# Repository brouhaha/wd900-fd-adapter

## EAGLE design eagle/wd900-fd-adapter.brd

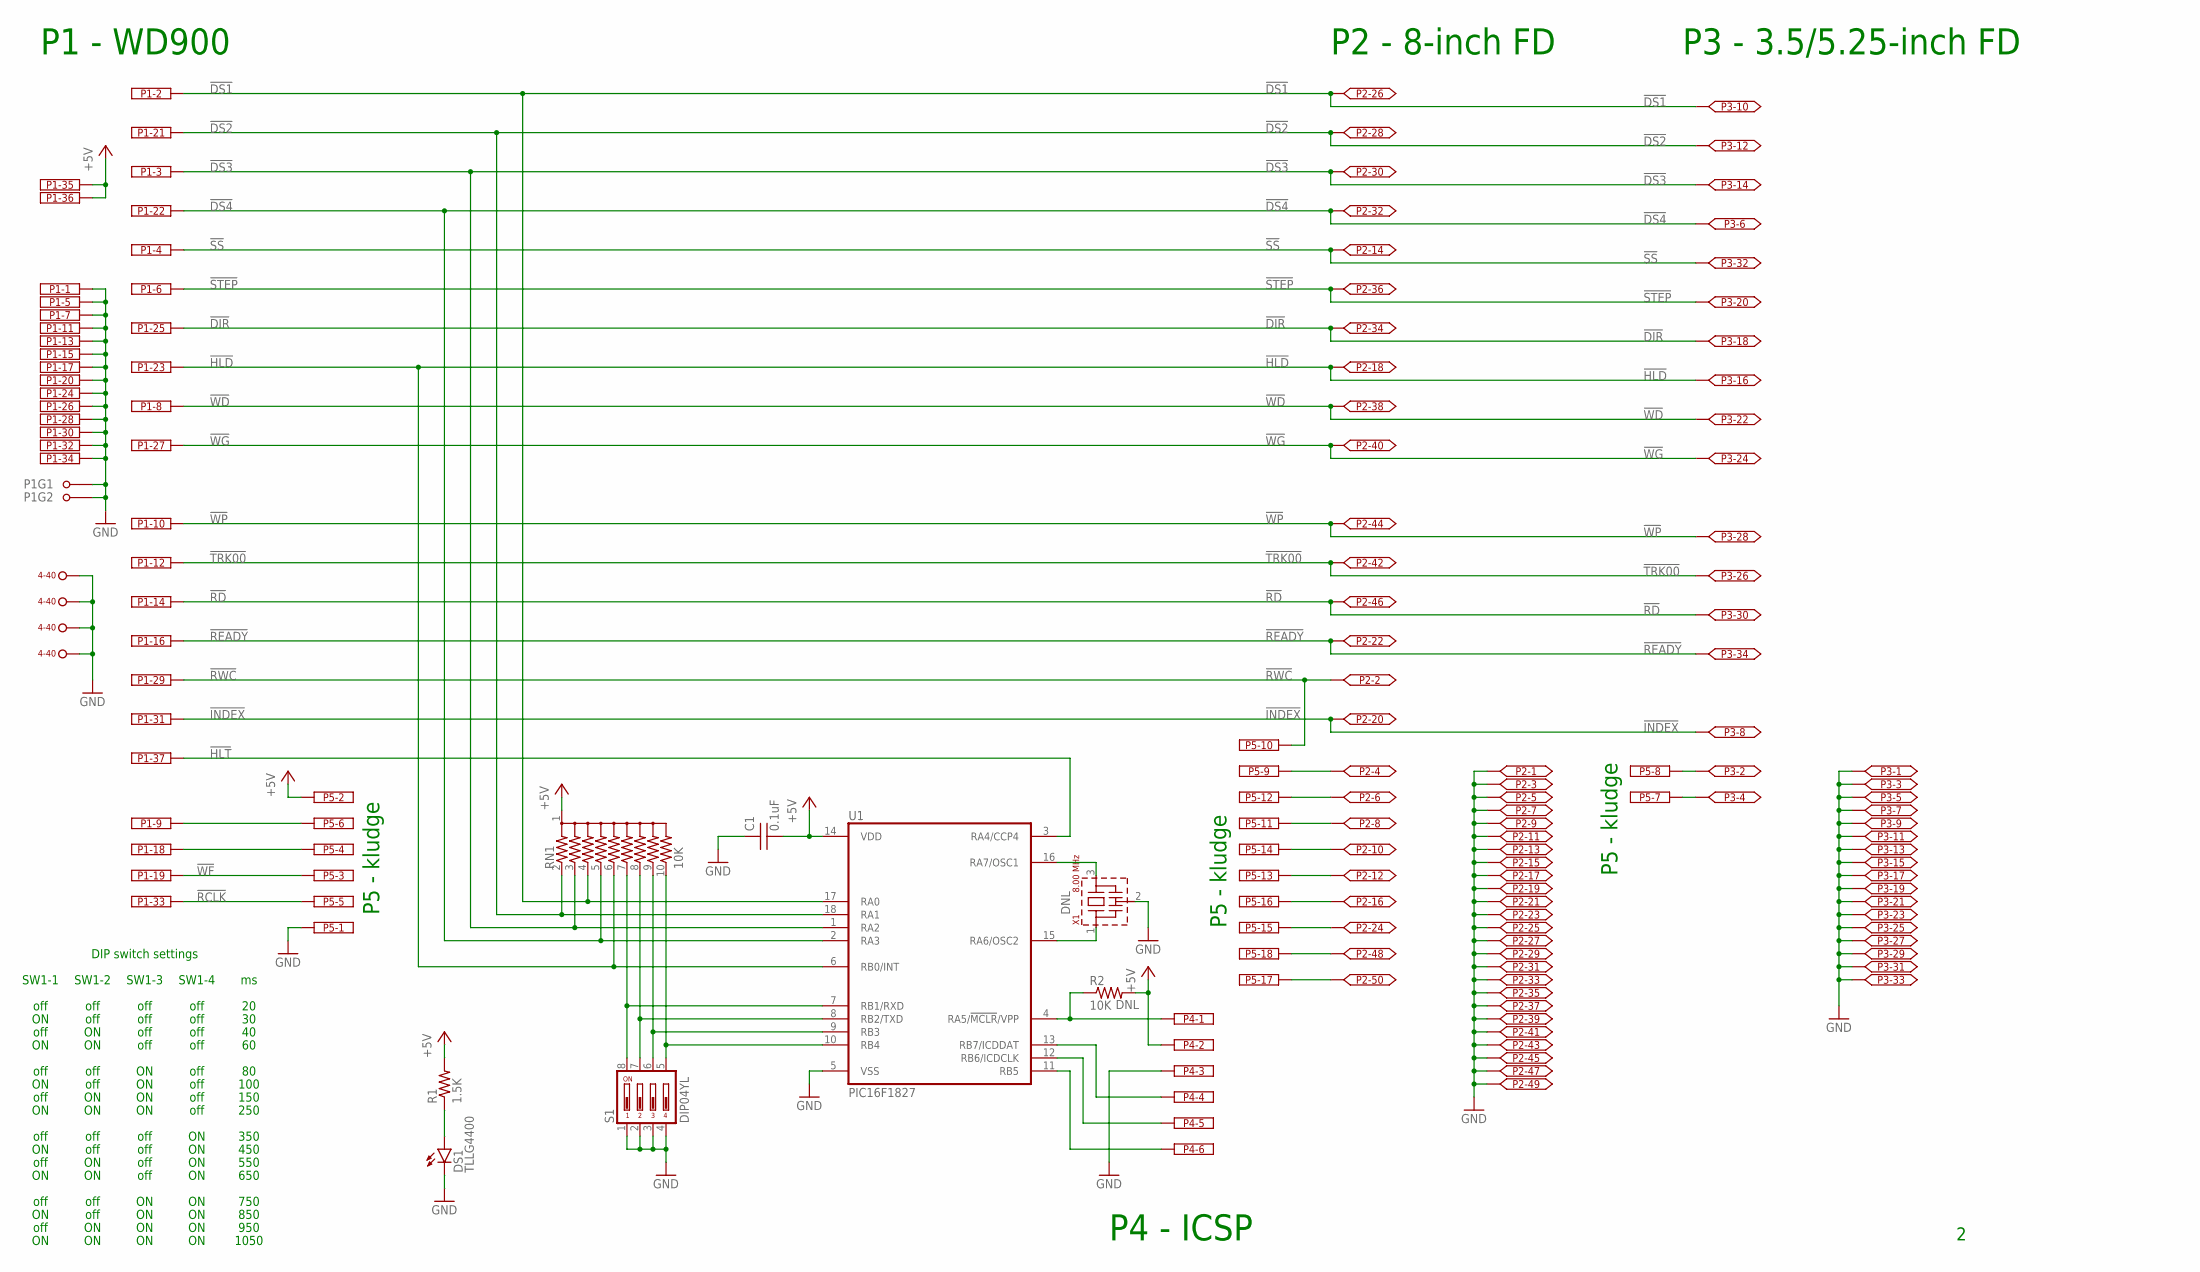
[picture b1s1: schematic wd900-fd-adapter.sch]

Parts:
C1: 0.1uF; C025-025X050
DS1: TLLG4400; LED3MM
H1, H2, H3, H4: HEX-4-40
P1: M37HPS; M37HP
P2: HDR-VS-2R-50
P3: HDR-VS-2R-34
P4: PIC ICSP; HDR-PIC-ICSP
P5: HDR-09-2
R1: 1.5K; 0207/10
R2: 10K; 0207/10
RN1: 10K; SIL10
S1: DIP04YL
U1: PIC16F1827; DIL18
X1: 8.00 MHz; CSTLS_G9

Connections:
!DIR: P1.25 (KL), P2.34, P3.18
!DS1: P1.2 (KL), P2.26, P3.10, RN1.4, U1.17 (RA0)
!DS2: P1.21 (KL), P2.28, P3.12, RN1.2, U1.18 (RA1)
!DS3: P1.3 (KL), P2.30, P3.14, RN1.3, U1.1 (RA2)
!DS4: P1.22 (KL), P2.32, P3.6, RN1.5, U1.2 (RA3)
!HLD: P1.23 (KL), P2.18, P3.16, RN1.6, U1.6 (RB0/INT)
!HLT: P1.37 (KL), U1.3 (RA4/CCP4)
!INDEX: P1.31 (KL), P2.20, P3.8
!RCLK: P1.33 (KL), P5.5
!RD: P1.14 (KL), P2.46, P3.30
!READY: P1.16 (KL), P2.22, P3.34
!RWC: P1.29 (KL), P2.2, P5.10
!SS: P1.4 (KL), P2.14, P3.32
!STEP: P1.6 (KL), P2.36, P3.20
!TRK00: P1.12 (KL), P2.42, P3.26
!WD: P1.8 (KL), P2.38, P3.22
!WF: P1.19 (KL), P5.3
!WG: P1.27 (KL), P2.40, P3.24
!WP: P1.10 (KL), P2.44, P3.28
+5V: C1.2, P1.35 (KL), P1.36 (KL), P4.2, P5.2, R1.2, R2.2, RN1.1, U1.14 (VDD)
GND: C1.1, DS1.K (C), H1.1, H2.1, H3.1, H4.1, P1.1 (KL), P1.5 (KL), P1.7 (KL), P1.11 (KL), P1.13 (KL), P1.15 (KL), P1.17 (KL), P1.20 (KL), P1.24 (KL), P1.26 (KL), P1.28 (KL), P1.30 (KL), P1.32 (KL), P1.34 (KL), P1.G1 (G2), P1.G2, P2.1, P2.3, P2.5, P2.7, P2.9, P2.11, P2.13, P2.15, P2.17, P2.19, P2.21, P2.23, P2.25, P2.27, P2.29, P2.31, P2.33, P2.35, P2.37, P2.39, P2.41, P2.43, P2.45, P2.47, P2.49, P3.1, P3.3, P3.5, P3.7, P3.9, P3.11, P3.13, P3.15, P3.17, P3.19, P3.21, P3.23, P3.25, P3.27, P3.29, P3.31, P3.33, P4.3, P5.1, S1.1, S1.2, S1.3, S1.4, U1.5 (VSS), X1.2 (VSS)
unnamed: P1.9 (KL), P5.6
unnamed: P1.18 (KL), P5.4
unnamed: RN1.7, S1.8, U1.7 (RB1/RXD)
unnamed: RN1.8, S1.7, U1.8 (RB2/TXD)
unnamed: RN1.9, S1.6, U1.9 (RB3)
unnamed: RN1.10, S1.5, U1.10 (RB4)
unnamed: P4.1, R2.1, U1.4 (RA5/!MCLR!/VPP)
unnamed: P4.4, U1.13 (RB7/ICDDAT)
unnamed: P4.5, U1.12 (RB6/ICDCLK)
unnamed: P4.6, U1.11 (RB5)
unnamed: U1.16 (RA7/OSC1), X1.3
unnamed: U1.15 (RA6/OSC2), X1.1
unnamed: P2.6, P5.12
unnamed: P2.8, P5.11
unnamed: P2.4, P5.9
unnamed: P2.10, P5.14
unnamed: P2.12, P5.13
unnamed: P2.24, P5.15
unnamed: P2.16, P5.16
unnamed: P2.50, P5.17
unnamed: P2.48, P5.18
unnamed: P3.4, P5.7
unnamed: P3.2, P5.8
unnamed: DS1.A, R1.1

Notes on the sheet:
P1 - WD900
P2 - 8-inch FD
P3 - 3.5/5.25-inch FD
DIP switch settings
off
SW1-1
SW1-2
SW1-3
SW1-4
100
150
250
350
450
550
650
750
850
950
1050
P4 - ICSP
P5 - kludge

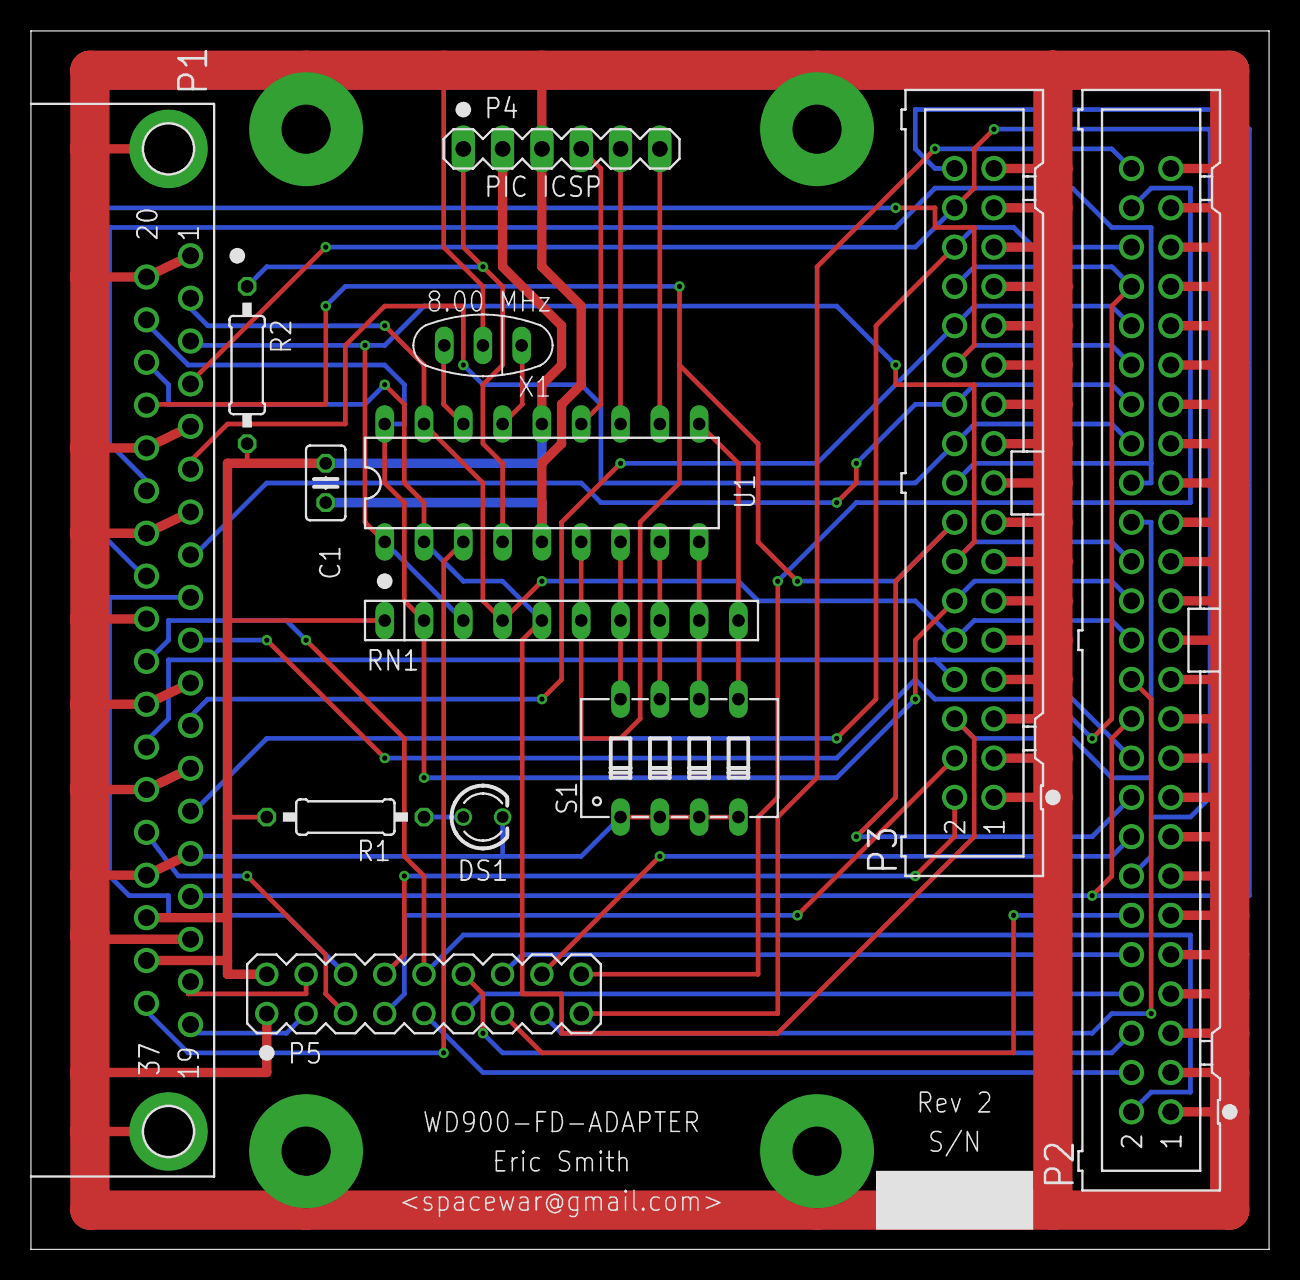
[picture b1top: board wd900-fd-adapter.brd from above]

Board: 2 copper layers, 80.0 x 78.7 mm, 17 parts (0 on the bottom side), 45 nets.

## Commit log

2015-12-19 Initial version.
2015-12-19 Added Eagle files for rev. 1 schematic and PCB.
2015-12-19 Updated Eagle files for rev. 2 schematic and PCB.

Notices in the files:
parts and their libraries:
wd900-fd-adapter: Copyright 2015 Eric Smith
